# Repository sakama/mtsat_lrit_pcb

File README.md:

# MTSAT LRIT PCB

#What's this?#

----------
MTSATのLRIT信号を受信するためのダウンコンバータ及びデコーダの回路図。Eagleで作成。

[Maker Faire Tokyo 2012](http://makezine.jp/)に出品予定。

こちらの記事に書いてあるものを基板に起こしたもの
[http://www.wa.commufa.jp/gigast/SAT/LRIT/LRIT.html](http://www.wa.commufa.jp/gigast/SAT/LRIT/LRIT.html)

# How to use #

----------

Please download CadSoft [EAGLE PCB](http://www.cadsoftusa.com/)

# About MTSAT LRIT #

http://www.jma.go.jp/jma/jma-eng/satellite/mtsat1r/4.3LRIT.pdf

## License ##

----------

Non-Commecial Use Only

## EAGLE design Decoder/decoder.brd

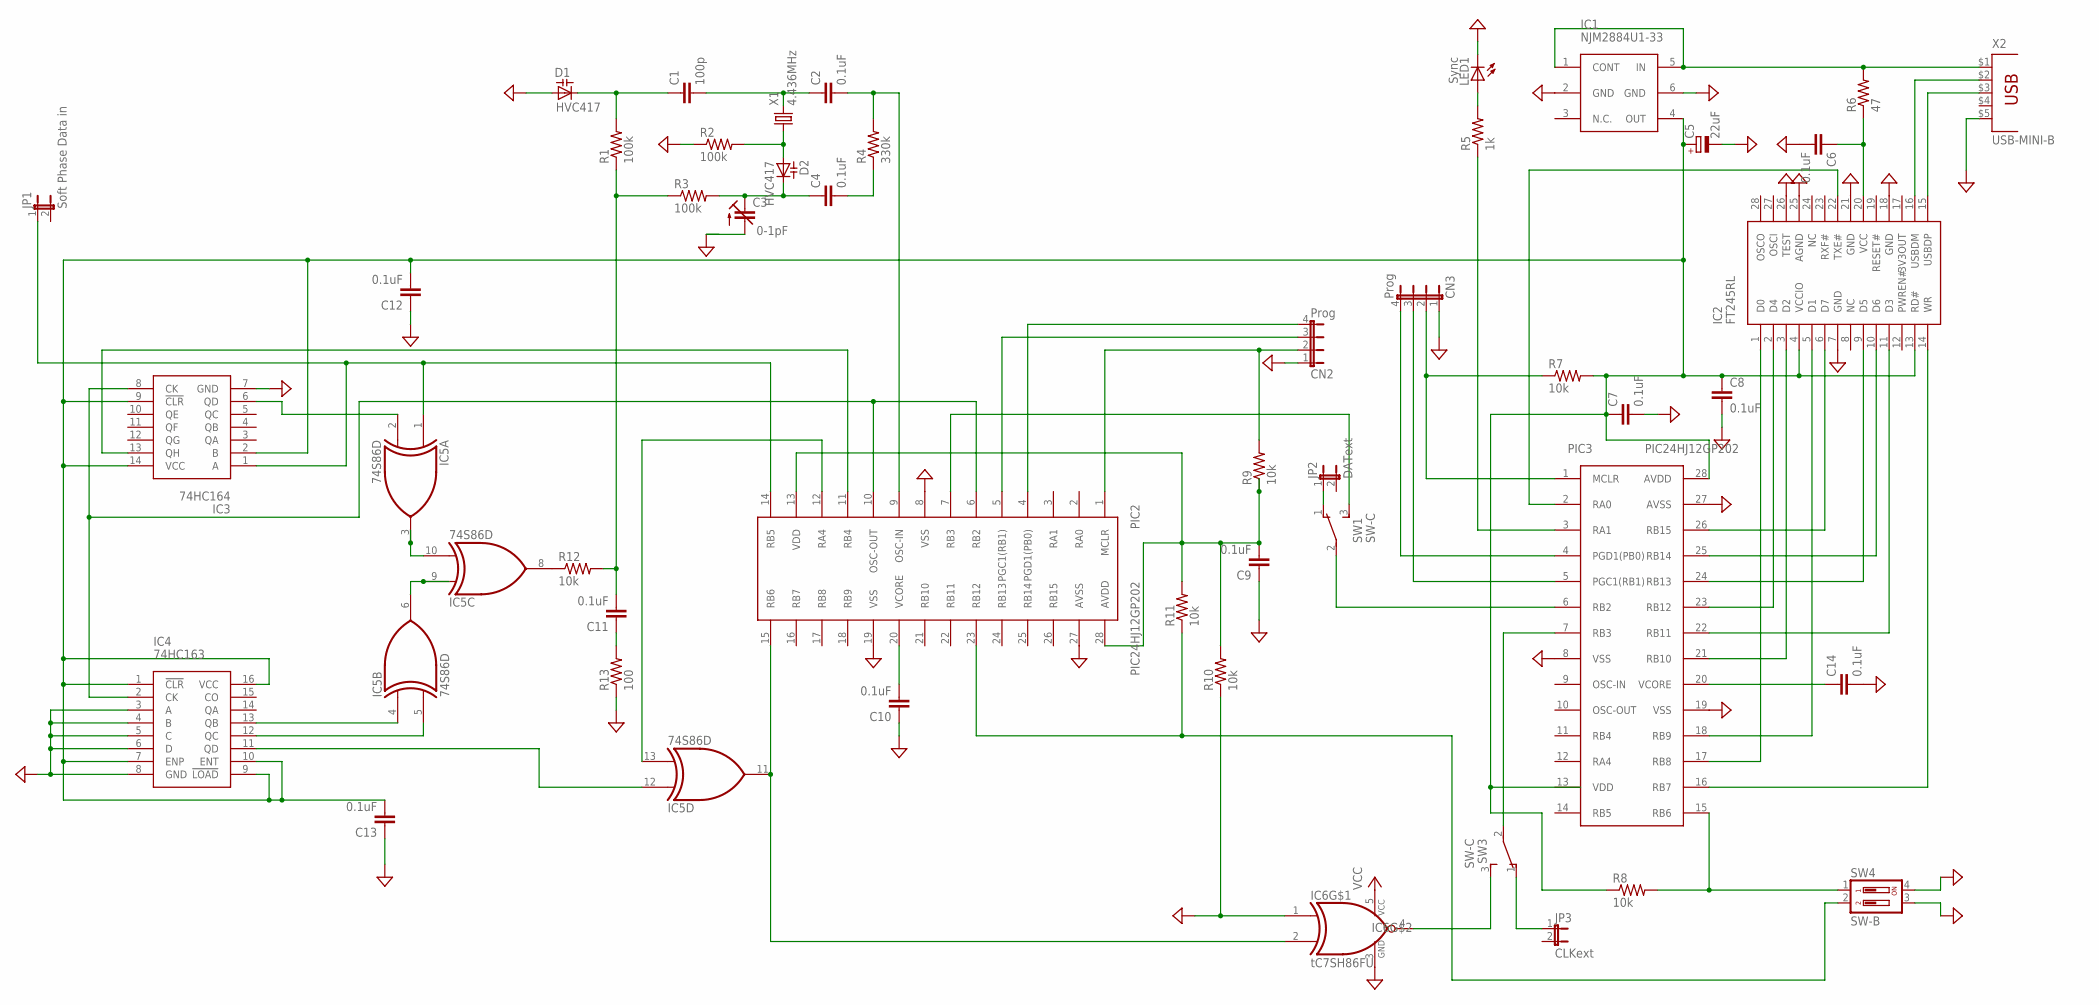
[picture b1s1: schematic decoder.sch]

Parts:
C1: 100p; C025-025X050
C2, C4, C6, C7, C8, C9, C10, C11, C12, C13, C14: 0.1uF; C050-025X075
C3: 0-1pF; CTRIMTZ03
C5: 22uF; E3,5-8
CN2, CN3: Prog; JP4
D1, D2: HVC417; SOT54H
IC1: NJM2884U1-33
IC2: FT245RL
IC3: 74HC164
IC4: 74HC163
IC5: 74S86D; SO14
IC6: tC7SH86FU; TC7SH86FU
JP1: Soft Phase Data in; JP1
JP2: DAText; JP1
JP3: CLKext; JP1
LED1: Sync; LED5MM
PIC2, PIC3: PIC24HJ12GP202
R1, R2, R3: 100k; 0207/7
R4: 330k; 0207/7
R5: 1k; 0207/7
R6: 47; 0207/7
R7, R8, R9, R10, R11, R12: 10k; 0207/7
R13: 100; 0207/7
SW1, SW3: SW-C; TL3XPO
SW4: SW-B; DIP02YL
X1: 4.436MHz; HC49/S
X2: USB-MINI-B

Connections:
GND: C3.2 (A), C5.-, C6.2, C7.2, C8.2, C9.1, C10.1, C12.1, C13.1, C14.2, CN2.1, CN3.1, D1.A, IC1.2 (GND), IC1.6 (GND), IC2.7 (GND), IC2.18 (GND), IC2.21 (GND), IC2.25 (AGND), IC2.26 (TEST), IC3.7 (GND), IC4.3 (A), IC4.4 (B), IC4.5 (C), IC4.6 (D), IC4.8 (GND), IC5.7 (GND), IC6.1 (I0), IC6.3 (GND), LED1.K (C), PIC2.8 (VSS), PIC2.19 (VSS), PIC2.27 (AVSS), PIC3.8 (VSS), PIC3.19 (VSS), PIC3.27 (AVSS), R2.1, R10.1, R13.1, SW4.3, SW4.4, X2.$5 (5)
unnamed: IC1.1 (CONT), IC1.5 (IN), R6.2, X2.$1 (1)
unnamed: C4.2, R4.1
unnamed: C1.2, C2.1, X1.2
unnamed: C2.2, PIC2.9 (OSC-IN), R4.2
unnamed: CN2.2, PIC2.1 (MCLR), R9.2
unnamed: C3.1 (E), C4.1, D2.C, R3.2
unnamed: C1.1, D1.C, R1.2
unnamed: IC5.8 (O), R12.1
unnamed: C10.2, PIC2.20 (VCORE)
unnamed: PIC2.23 (RB12), R11.1, SW4.2
unnamed: PIC3.15 (RB6), R8.2, SW4.1
unnamed: C11.1, R13.2
unnamed: PIC2.7 (RB3), SW1.3 (S)
unnamed: PIC3.6 (RB2), SW1.2
unnamed: IC5.11 (O), IC6.2 (I1), PIC2.15 (RB6)
unnamed: PIC3.3 (RA1), R5.1
unnamed: PIC3.7 (RB3), SW3.2
unnamed: C9.2, PIC2.13 (VDD), PIC2.28 (AVDD), R9.1, R10.2, R11.2
unnamed: IC2.22 (TXE#), PIC3.2 (RA0)
unnamed: C11.2, R1.1, R3.1, R12.2
unnamed: IC5.6 (O), IC5.9 (I0)
unnamed: IC5.3 (O), IC5.10 (I1)
unnamed: IC3.1 (A), IC5.1 (I0), JP1.1, PIC2.14 (RB5)
unnamed: IC5.13 (I1), PIC2.12 (RA4)
unnamed: IC2.14 (WR), PIC3.16 (RB7)
unnamed: D2.A, R2.2, X1.1
unnamed: IC2.10 (D6), PIC3.25 (RB14)
unnamed: IC2.15 (USBDP), X2.$3 (3)
unnamed: IC2.16 (USBDM), X2.$2 (2)
unnamed: IC2.11 (D3), PIC3.22 (RB11)
unnamed: IC2.9 (D5), PIC3.24 (RB13)
unnamed: IC2.1 (D0), PIC3.17 (RB8)
unnamed: IC2.2 (D4), PIC3.23 (RB12)
unnamed: IC2.3 (D2), PIC3.21 (RB10)
unnamed: IC2.5 (D1), PIC3.18 (RB9)
unnamed: IC2.6 (D7), PIC3.26 (RB15)
unnamed: IC3.6 (QD), IC5.2 (I1)
unnamed: IC3.13 (QH), PIC2.11 (RB4)
unnamed: IC4.13 (QB), IC5.4 (I0)
unnamed: IC4.12 (QC), IC5.5 (I1)
unnamed: IC4.11 (QD), IC5.12 (I0)
unnamed: JP3.1, SW3.1 (O)
unnamed: C5.+, C7.1, C8.1, C12.2, C13.2, IC1.4 (OUT), IC2.4 (VCCIO), IC2.13 (RD#), IC3.2 (B), IC3.9 (!CLR), IC3.14 (VCC), IC4.1 (!CLR), IC4.7 (ENP), IC4.9 (!LOAD), IC4.10 (ENT), IC4.16 (VCC), PIC3.28 (AVDD), R7.2, R8.1
unnamed: IC3.8 (CK), IC4.2 (CK), PIC2.6 (RB2), PIC2.10 (OSC-OUT)
unnamed: C6.1, IC2.20 (VCC), R6.1
unnamed: CN2.3, PIC2.5 (PGC1(RB1))
unnamed: CN2.4, PIC2.4 (PGD1(PB0))
unnamed: CN3.2, PIC3.1 (MCLR), R7.1
unnamed: CN3.3, PIC3.5 (PGC1(RB1))
unnamed: CN3.4, PIC3.4 (PGD1(PB0))
unnamed: LED1.A, R5.2
unnamed: JP2.1, SW1.1 (O)
unnamed: IC6.4 (O), SW3.3 (S)
unnamed: C14.1, PIC3.20 (VCORE)
VCC: IC5.14 (VCC), IC6.5 (VCC)
VDD: PIC3.13 (VDD)

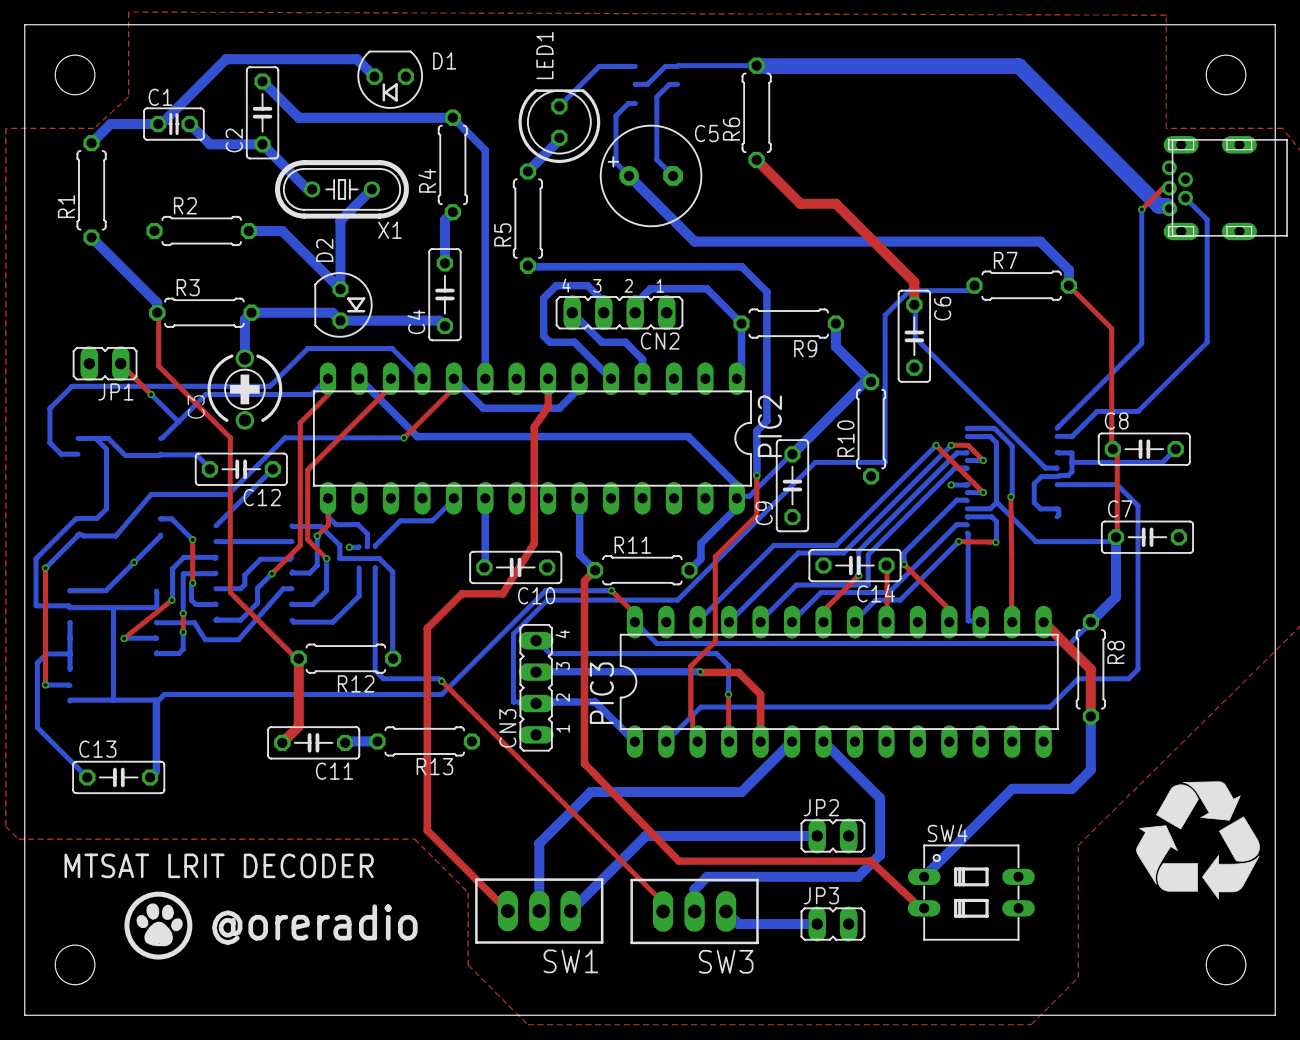
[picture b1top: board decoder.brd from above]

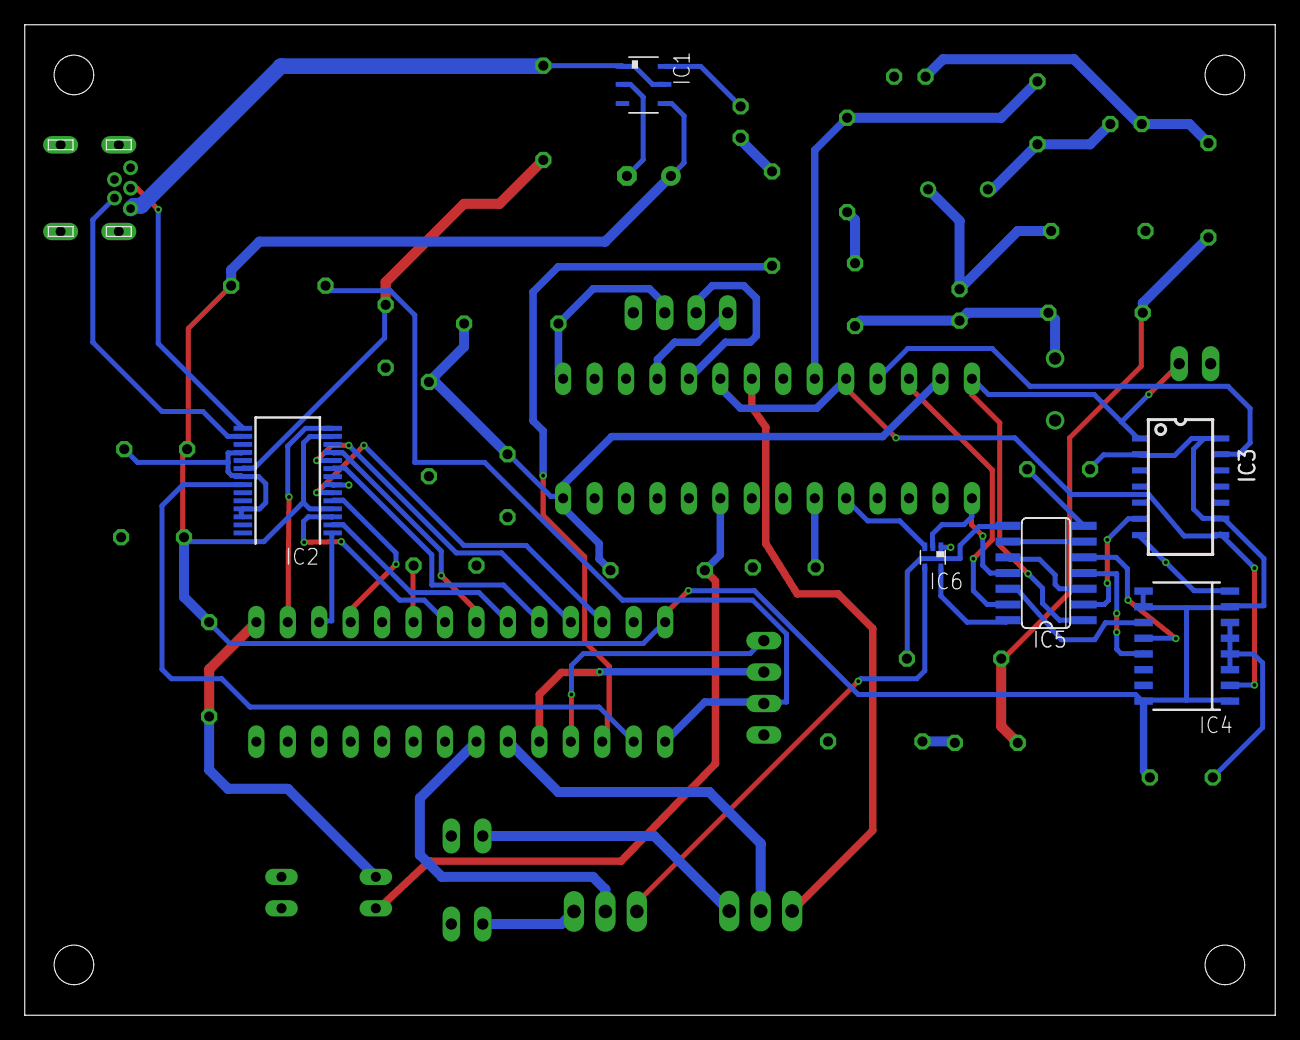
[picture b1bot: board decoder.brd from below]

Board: 2 copper layers, 101.0 x 80.0 mm, 50 parts (6 on the bottom side), 56 nets.

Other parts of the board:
U$36: LOGO
U$38: RECYCLING_10.00

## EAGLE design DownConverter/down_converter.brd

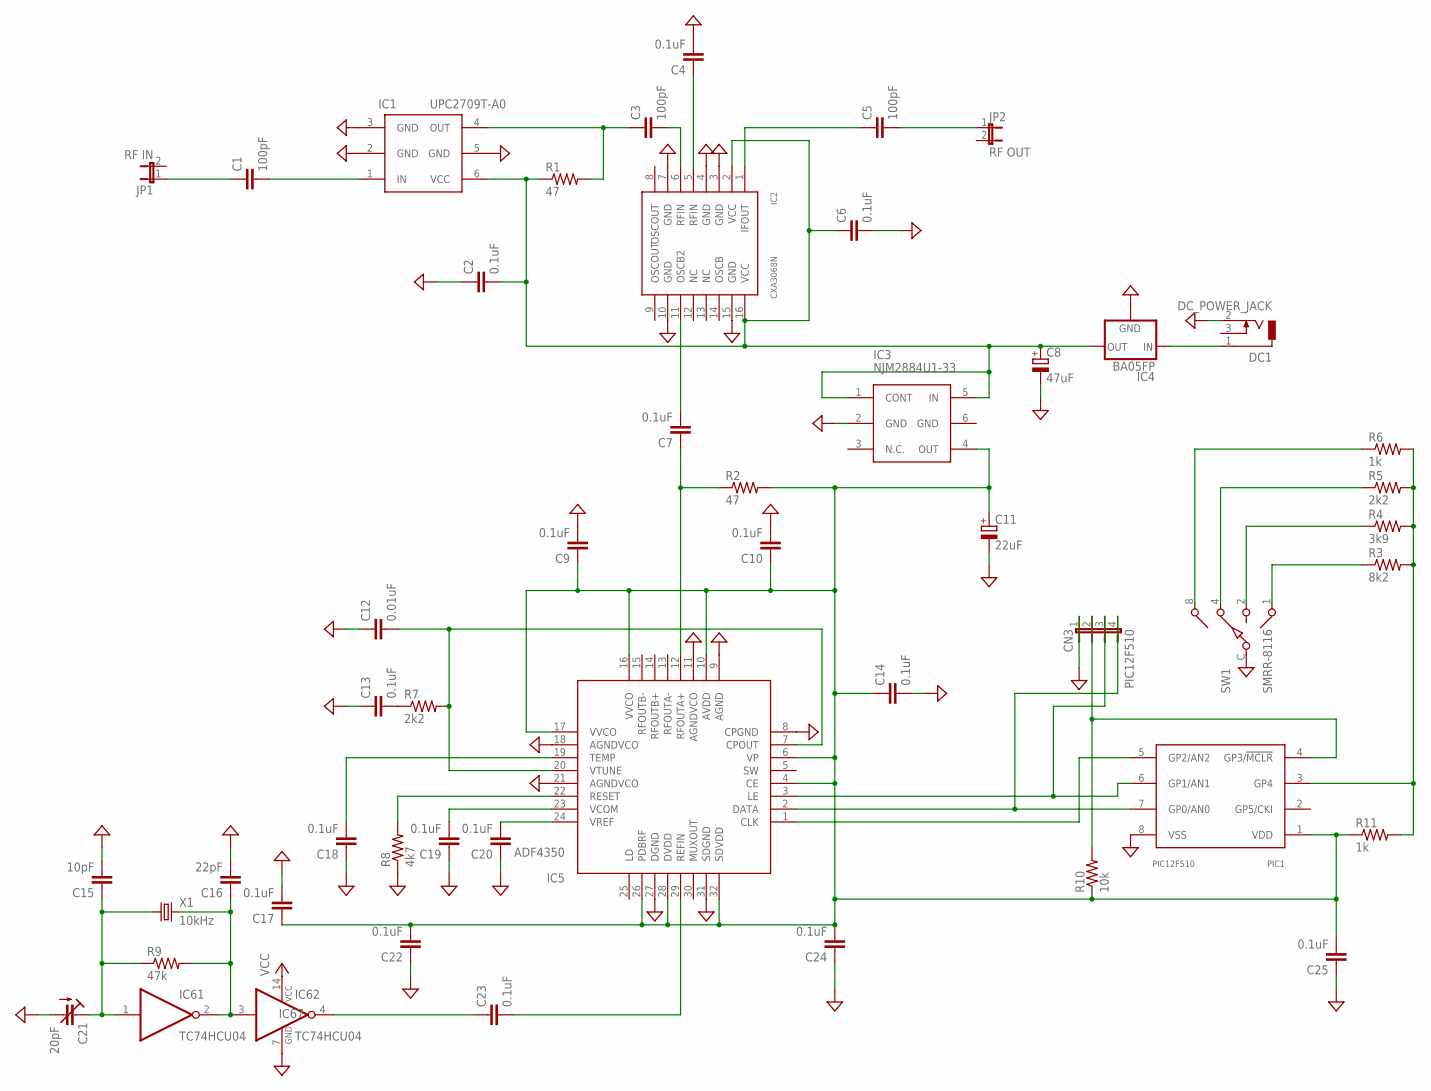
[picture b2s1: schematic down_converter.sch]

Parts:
C1, C3, C5: 100pF; C025-025X050
C2, C4, C6, C7, C9, C10, C13, C14, C17, C18, C19, C20, C22, C23, C24, C25: 0.1uF; C050-025X075
C8: 47uF; E5-10,5
C11: 22uF; E3,5-8
C12: 0.01uF; C025-025X050
C15: 10pF; C025-025X050
C16: 22pF; C025-025X050
C21: 20pF; CTRIMTZ03
CN3: PIC12F510; JP4
DC1: DC_POWER_JACK
IC1: UPC2709T-A0; SOT23-6
IC2: CXA3068N
IC3: NJM2884U1-33
IC4: BA05FP
IC5: ADF4350
IC6: TC74HCU04
JP1: RF IN; JP1
JP2: RF OUT; JP1
PIC1: PIC12F510; PIC12F1288
R1, R2: 47; 0207/7
R3: 8k2; 0207/7
R4: 3k9; 0207/7
R5, R7: 2k2; 0207/7
R6, R11: 1k; 0207/7
R8: 4k7; 0207/7
R9: 47k; 0207/7
R10: 10k; 0207/7
SW1: SMRR-8116; SW-C16
X1: 10kHz; HC49/S

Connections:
GND: C2.1, C4.2, C6.2, C8.-, C9.2, C10.2, C11.-, C12.1, C13.1, C14.2, C15.2, C16.2, C17.2, C18.1, C19.1, C20.1, C21.2 (A), C22.1, C24.1, C25.1, CN3.1, DC1.2, IC1.2 (GND), IC1.3 (GND), IC1.5 (GND), IC2.3 (GND), IC2.4 (GND), IC2.7 (GND), IC2.10 (GND), IC2.15 (GND), IC3.2 (GND), IC3.6 (GND), IC4.2 (GND), IC5.8 (CPGND), IC5.9 (AGND), IC5.11 (AGNDVCO), IC5.18 (AGNDVCO), IC5.21 (AGNDVCO), IC5.27 (DGND), IC5.31 (SDGND), IC6.7 (GND), PIC1.8 (VSS), R8.1, SW1.C
unnamed: C13.2, R7.1
unnamed: DC1.1, IC4.1 (IN)
unnamed: C23.2, IC5.29 (REFIN)
unnamed: C20.2, IC5.24 (VREF)
unnamed: C19.2, IC5.23 (VCOM)
unnamed: IC5.22 (RESET), R8.2
unnamed: C18.2, IC5.19 (TEMP)
unnamed: C12.2, IC5.7 (CPOUT), IC5.20 (VTUNE), R7.2
unnamed: C7.1, IC5.12 (RFOUTA+), R2.1
unnamed: C2.2, C6.1, C8.+, IC1.6 (VCC), IC2.2 (VCC), IC2.16 (VCC), IC3.1 (CONT), IC3.5 (IN), IC4.3 (OUT), R1.1
unnamed: IC5.1 (CLK), PIC1.5 (GP2/AN2)
unnamed: PIC1.3 (GP4), R3.2, R4.2, R5.2, R6.2, R11.2
unnamed: C7.2, IC2.11 (OSCB2)
unnamed: C3.1, IC1.4 (OUT), R1.2
unnamed: C1.2, IC1.1 (IN)
unnamed: C3.2, IC2.6 (RFIN)
unnamed: C4.1, IC2.5 (RFIN)
unnamed: C5.1, IC2.1 (IFOUT)
unnamed: R6.1, SW1.8
unnamed: CN3.2, PIC1.4 (GP3/!MCLR), R10.2
unnamed: R5.1, SW1.4
unnamed: R4.1, SW1.2
unnamed: R3.1, SW1.1
unnamed: CN3.3, IC5.3 (LE), PIC1.6 (GP1/AN1)
unnamed: C5.2, JP2.1
unnamed: C1.1, JP1.1
unnamed: C9.1, C10.1, C11.+, C14.1, C17.1, C22.2, C24.2, C25.2, IC3.4 (OUT), IC5.4 (CE), IC5.6 (VP), IC5.10 (AVDD), IC5.16 (VVCO), IC5.17 (VVCO), IC5.26 (PDBRF), IC5.28 (DVDD), IC5.32 (SDVDD), PIC1.1 (VDD), R2.2, R10.1, R11.1
unnamed: C16.1, IC6.2 (Y), IC6.3 (A), R9.2, X1.2
unnamed: C15.1, C21.1 (E), IC6.1 (A), R9.1, X1.1
unnamed: C23.1, IC6.4 (Y)
unnamed: CN3.4, IC5.2 (DATA), PIC1.7 (GP0/AN0)
VCC: IC6.14 (VCC)

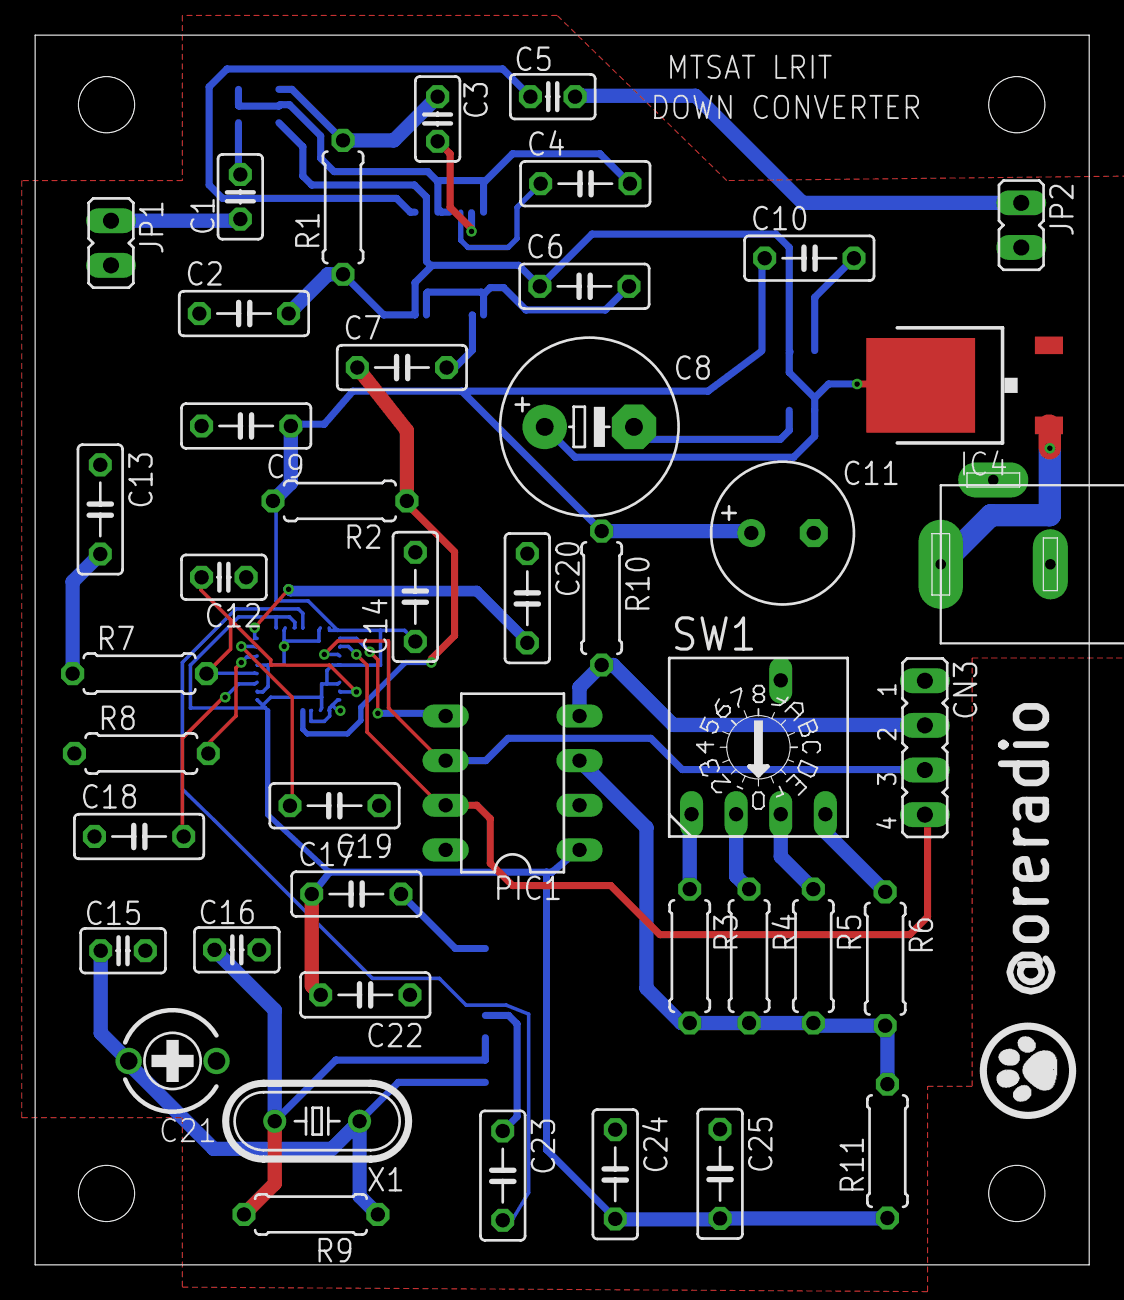
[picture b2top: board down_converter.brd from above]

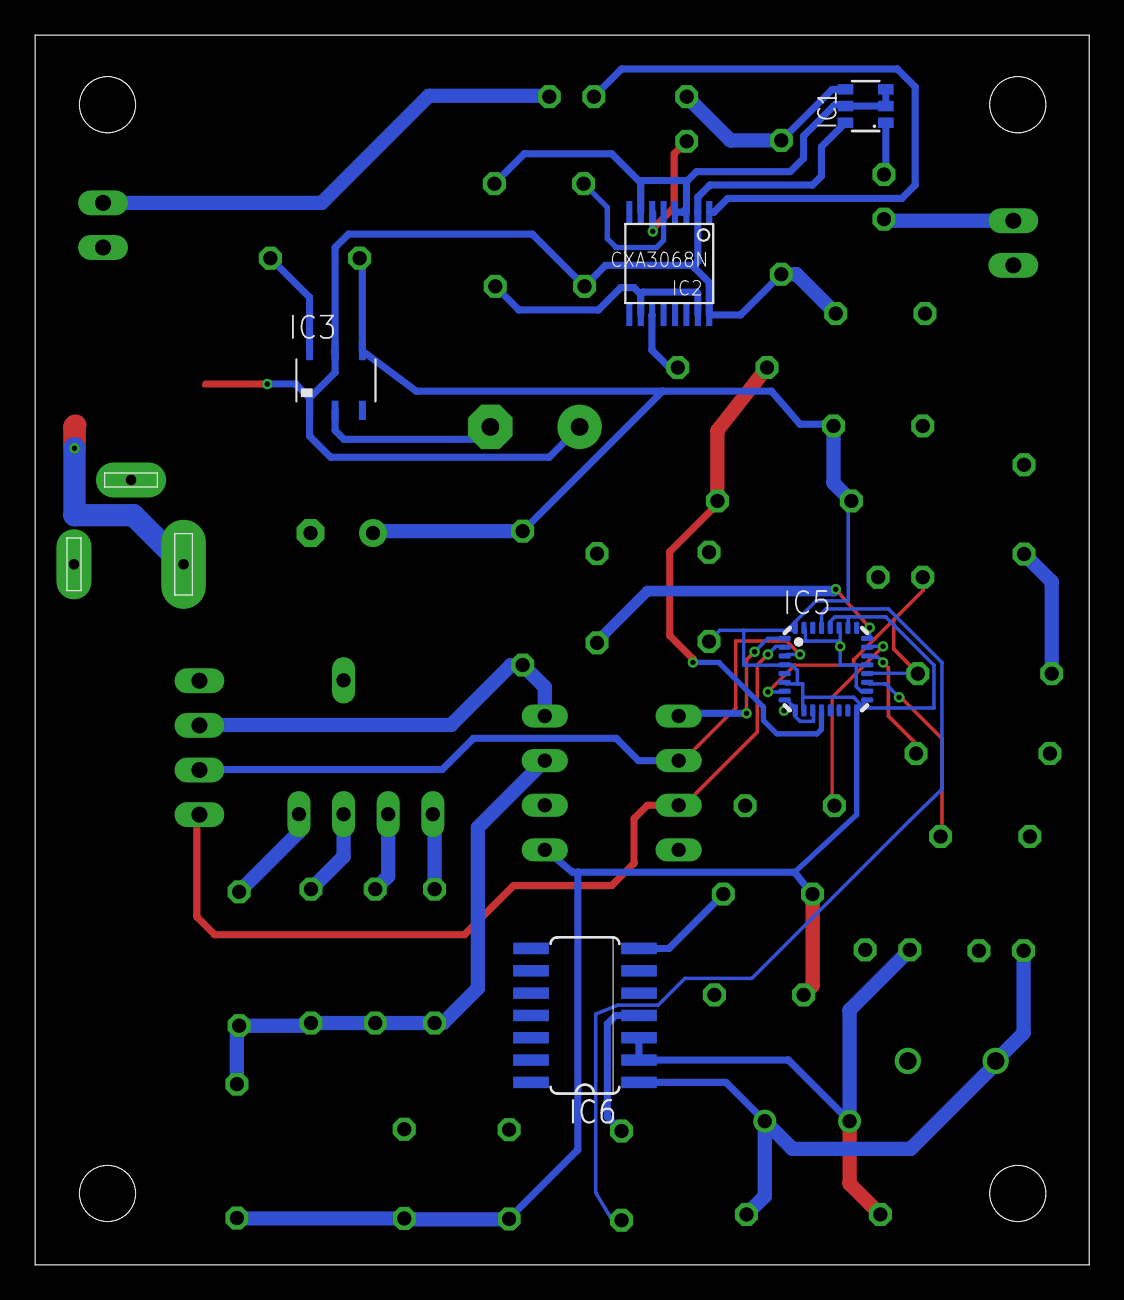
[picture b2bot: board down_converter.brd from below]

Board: 2 copper layers, 60.0 x 70.0 mm, 50 parts (5 on the bottom side), 32 nets.

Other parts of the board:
U$40: LOGO

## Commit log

2012-11-16 プロジェクト作成
